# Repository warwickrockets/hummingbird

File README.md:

# Hummingbird

There will eventually be three folders here: ./sims for simulations (Matlab/Simulink mostly), ./myRIO for control software written for the NI MyRIO (might be Labview VIs, C/C++, or a hideous mixture of the two if that's possible), and ./teensy for control software written for a Teensy-3.1-based flight computer. For now, there's just a README. Ho hum.

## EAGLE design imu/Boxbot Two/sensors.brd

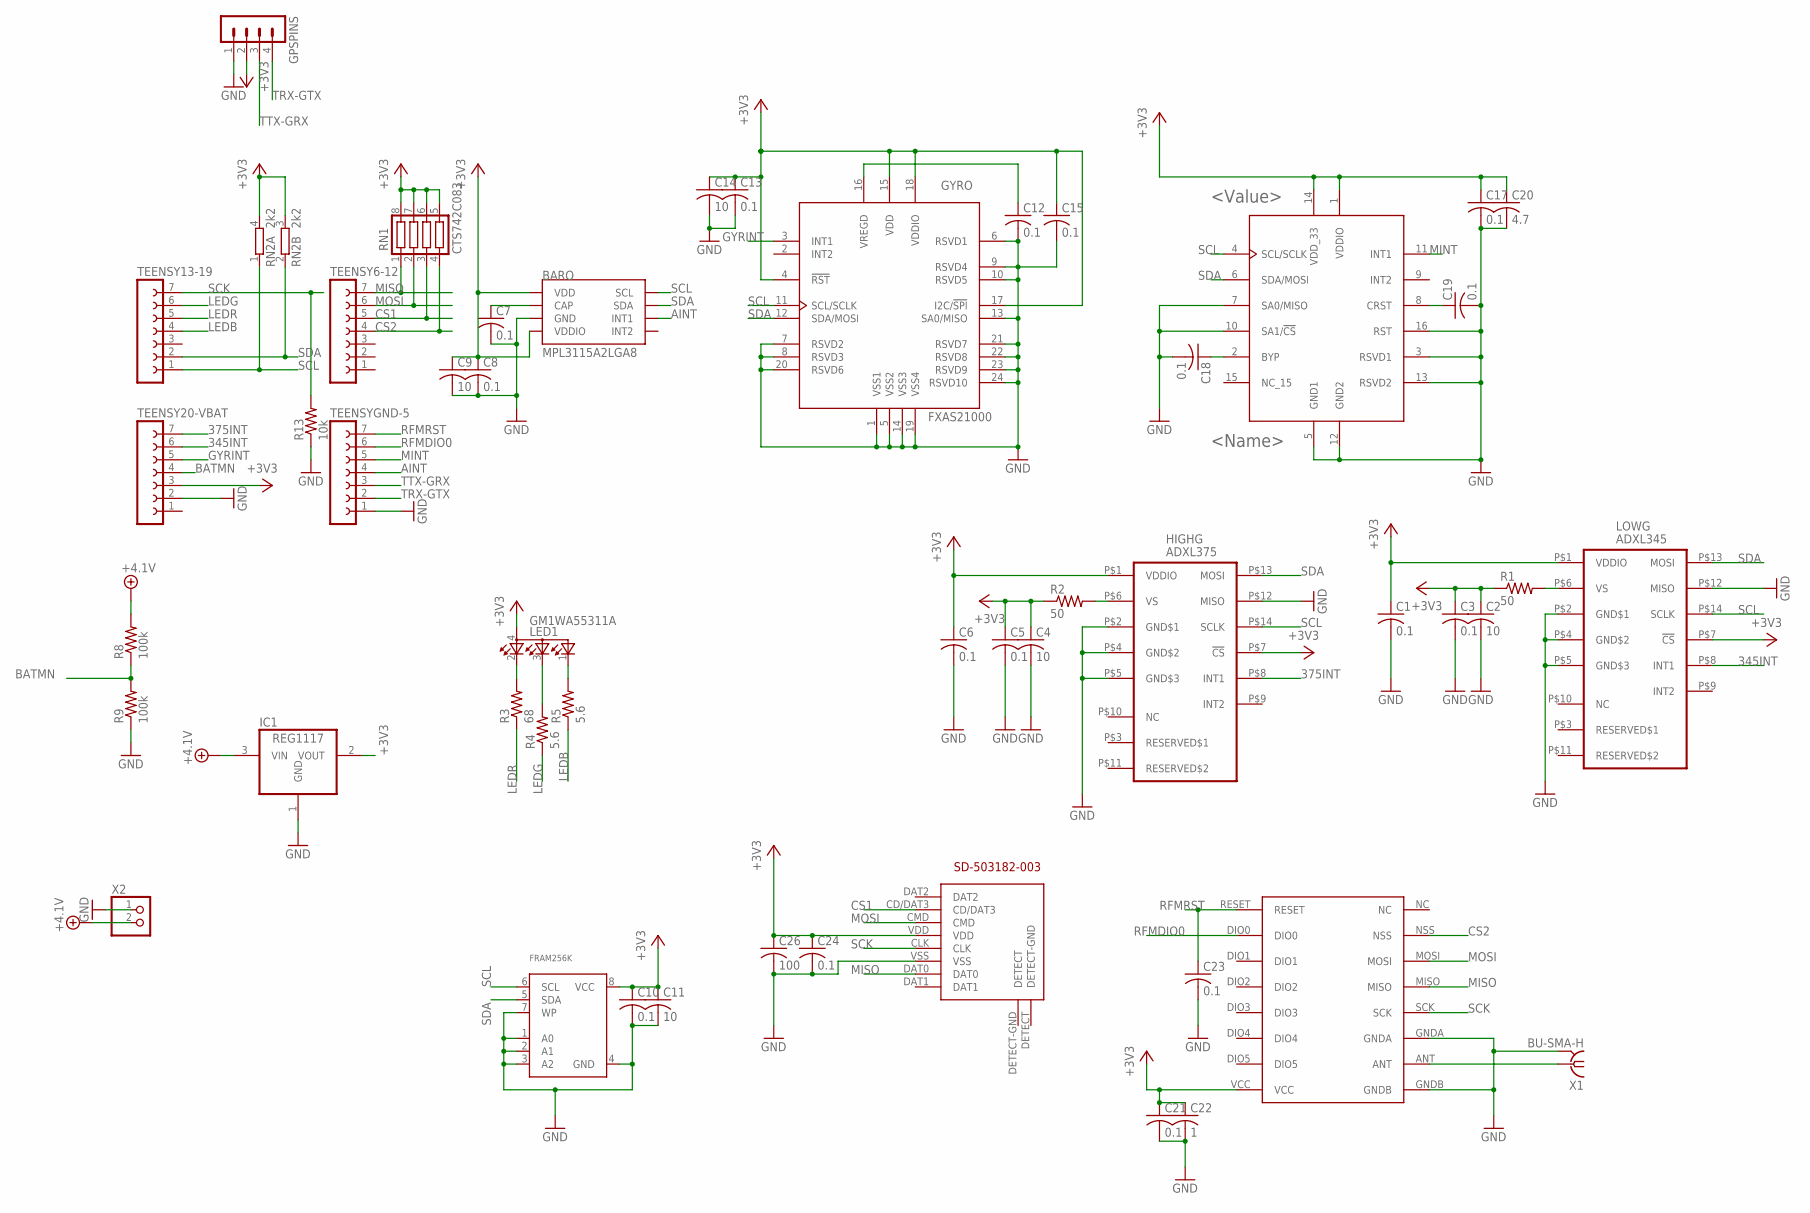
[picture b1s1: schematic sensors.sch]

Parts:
BARO: MPL3115A2LGA8; LGA8
C1, C3, C5, C6, C7, C8, C10, C12, C13, C15, C17, C18, C19, C21, C23, C24: 0.1; C0603
C2, C4, C9, C11, C14: 10; C0805
C20: 4.7; C0805
C22: 1; C0805
C26: 100; C0805
FRAM256K: FRAM_SOIC8_I2C; SOIC8_208MIL
GPSPINS: MA04-1
GYRO: FXAS21000; QFN24_0P5_4X4_ASYM_EXP
HIGHG: ADXL375; LGA14
IC1: REG1117; SOT223
LED1: GM1WA55311A
LOWG: ADXL345; LGA14
MAG: FXOS870CQ; QFN16_0P5_3X3
R1, R2: 50; R0805
R3: 68; R0805
R4, R5: 5.6; R0805
R8, R9: 100k; R0805
R13: 10k; R0805
RN1: CTS742C083
RN2: 2k2; EXBV4V
TEENSY6-12, TEENSY13-19, TEENSY20-VBAT: FE07-1; FE07
TEENSYGND-5: FE07-1; FE07
U$1: SD-503182-003
U$2: RFM69HW; RFM
X1: BU-SMA-H
X2: CON_JST_PH_2PIN; JSTPH2

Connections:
345INT: LOWG.P$8 (INT1), TEENSY20-VBAT.6
375INT: HIGHG.P$8 (INT1), TEENSY20-VBAT.7
+3V3: BARO.1 (VDD), BARO.4 (VDDIO), C1.1, C2.1, C3.1, C4.1, C5.1, C6.1, C8.1, C9.1, C10.1, C11.1, C13.1, C14.1, C15.1, C17.1, C20.1, C21.1, C22.1, C24.1, C26.1, FRAM256K.8 (VCC), GPSPINS.2, GYRO.4 (!RST), GYRO.15 (VDD), GYRO.17 (I2C/!SPI), GYRO.18 (VDDIO), HIGHG.P$1 (VDDIO), HIGHG.P$7 (!CS), IC1.2 (VOUT), LED1.4 (A), LOWG.P$1 (VDDIO), LOWG.P$7 (!CS), MAG.1 (VDDIO), MAG.14 (VDD_33), R1.1, R2.1, RN1.5, RN1.6, RN1.7, RN1.8, RN2.3 (2), RN2.4 (2), TEENSY20-VBAT.3, U$1.VDD, U$2.VCC
+4.1V: IC1.3 (VIN), R8.2, X2.2
AINT: BARO.6 (INT1), TEENSYGND-5.4
BATMN: R8.1, R9.2, TEENSY20-VBAT.4
CS1: RN1.3, TEENSY6-12.5, U$1.CD/DAT3
CS2: RN1.4, TEENSY6-12.4, U$2.NSS
GND: BARO.3 (GND), C1.2, C2.2, C3.2, C4.2, C5.2, C6.2, C7.2, C8.2, C9.2, C10.2, C11.2, C12.2, C13.2, C14.2, C15.2, C17.2, C18.2, C19.2, C20.2, C21.2, C22.2, C23.2, C24.2, C26.2, FRAM256K.1 (A0), FRAM256K.2 (A1), FRAM256K.3 (A2), FRAM256K.4 (GND), FRAM256K.7 (WP), GPSPINS.1, GYRO.1 (VSS1), GYRO.5 (VSS2), GYRO.6 (RSVD1), GYRO.7 (RSVD2), GYRO.8 (RSVD3), GYRO.9 (RSVD4), GYRO.10 (RSVD5), GYRO.13 (SA0/MISO), GYRO.14 (VSS3), GYRO.19 (VSS4), GYRO.20 (RSVD6), GYRO.21 (RSVD7), GYRO.22 (RSVD8), GYRO.23 (RSVD9), GYRO.24 (RSVD10), HIGHG.P$2 (GND$1), HIGHG.P$4 (GND$2), HIGHG.P$5 (GND$3), HIGHG.P$12 (MISO), IC1.1 (GND), LOWG.P$2 (GND$1), LOWG.P$4 (GND$2), LOWG.P$5 (GND$3), LOWG.P$12 (MISO), MAG.3 (RSVD1), MAG.5 (GND1), MAG.7 (SA0/MISO), MAG.10 (SA1/!CS), MAG.12 (GND2), MAG.13 (RSVD2), MAG.16 (RST), R9.1, R13.1, TEENSY20-VBAT.2, TEENSYGND-5.1, U$1.VSS, U$2.GNDA, U$2.GNDB, X1.2, X1.3 (2), X1.4 (2), X1.5 (2), X2.1
GYRINT: GYRO.3 (INT1), TEENSY20-VBAT.5
LEDB: R5.1, TEENSY13-19.4
LEDG: R4.1, TEENSY13-19.6
LEDR: R3.1, TEENSY13-19.5
MINT: MAG.11 (INT1), TEENSYGND-5.5
MISO: RN1.1, TEENSY6-12.7, U$1.DAT0, U$2.MISO
MOSI: RN1.2, TEENSY6-12.6, U$1.CMD, U$2.MOSI
unnamed: LOWG.P$6 (VS), R1.2
unnamed: HIGHG.P$6 (VS), R2.2
unnamed: LED1.2 (CRED), R3.2
unnamed: C18.1, MAG.2 (BYP)
unnamed: LED1.3 (CBLUE), R4.2
unnamed: LED1.1 (CGREEN), R5.2
unnamed: BARO.2 (CAP), C7.1
unnamed: C12.1, GYRO.16 (VREGD)
unnamed: C19.1, MAG.8 (CRST)
unnamed: U$2.ANT, X1.1
RFMDIO0: TEENSYGND-5.6, U$2.DIO0
RFMRST: C23.1, TEENSYGND-5.7, U$2.RESET
SCK: R13.2, TEENSY13-19.7, U$1.CLK, U$2.SCK
SCL: BARO.8 (SCL), FRAM256K.6 (SCL), GYRO.11 (SCL/SCLK), HIGHG.P$14 (SCLK), LOWG.P$14 (SCLK), MAG.4 (SCL/SCLK), RN2.1, TEENSY13-19.1
SDA: BARO.7 (SDA), FRAM256K.5 (SDA), GYRO.12 (SDA/MOSI), HIGHG.P$13 (MOSI), LOWG.P$13 (MOSI), MAG.6 (SDA/MOSI), RN2.2 (1), TEENSY13-19.2
TRX-GTX: GPSPINS.4, TEENSYGND-5.2
TTX-GRX: GPSPINS.3, TEENSYGND-5.3

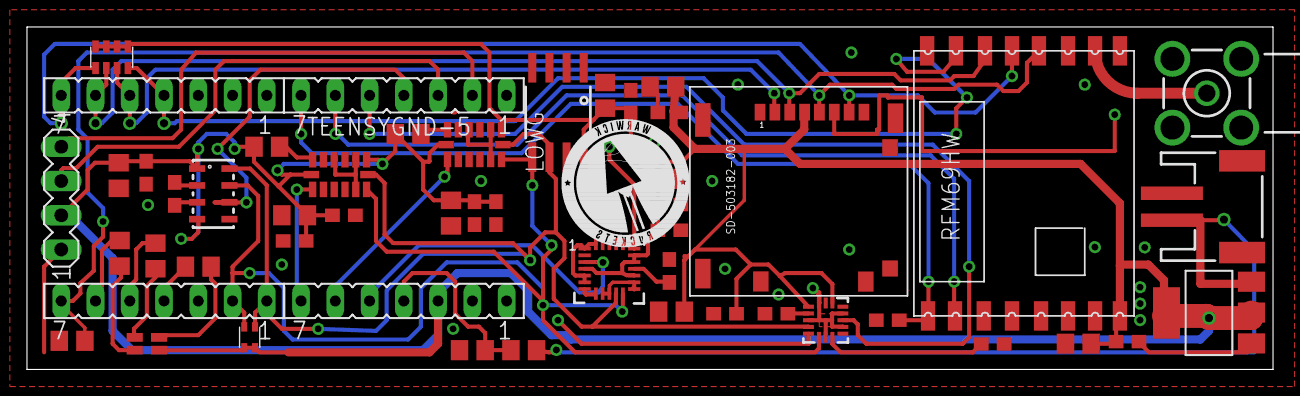
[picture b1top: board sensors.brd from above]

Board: 2 copper layers, 92.4 x 25.4 mm, 51 parts (0 on the bottom side), 33 nets.

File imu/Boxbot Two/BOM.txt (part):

Partlist exported from F:/Warwick Spaceflight/Projects/Hummingbird/Github/hummingbird/imu/Boxbot Two/sensors.sch at 14/06/2015 19:09:03

Part          Value         Device          Package                Description                                                     MF MPN     OC_FARNELL OC_NEWARK
BARO          MPL3115A2LGA8 MPL3115A2LGA8   LGA8                   Altimeter/Pressure Sensor, I2C, 1.95V-3.6V supply, 50 to 110kPa                                
C1            0.1           C-USC0603       C0603                  CAPACITOR, American symbol                                                                     
C2            10            C-USC0805       C0805                  CAPACITOR, American symbol                                                                     
C3            0.1           C-USC0603       C0603                  CAPACITOR, American symbol                                                                     
C4            10            C-USC0805       C0805                  CAPACITOR, American symbol                                                                     
C5            0.1           C-USC0603       C0603                  CAPACITOR, American symbol                                                                     
C6            0.1           C-USC0603       C0603                  CAPACITOR, American symbol                                                                     
C7            0.1           C-USC0603       C0603                  CAPACITOR, American symbol                                                                     
C8            0.1           C-USC0603       C0603                  CAPACITOR, American symbol                                                                     
C9            10            C-USC0805       C0805                  CAPACITOR, American symbol                                                                     
C10           0.1           C-USC0603       C0603                  CAPACITOR, American symbol                                                                     
C11           10            C-USC0805       C0805                  CAPACITOR, American symbol                                                                     
C12           0.1           C-USC0603       C0603                  CAPACITOR, American symbol                                                                     
C13           0.1           C-USC0603       C0603                  CAPACITOR, American symbol                                                                     
C14           10            C-USC0805       C0805                  CAPACITOR, American symbol                                                                     
C15           0.1           C-USC0603       C0603                  CAPACITOR, American symbol                                                                     
C17           0.1           C-USC0603       C0603                  CAPACITOR, American symbol                                                                     
C18           0.1           C-USC0603       C0603                  CAPACITOR, American symbol                                                                     
C19           0.1           C-USC0603       C0603                  CAPACITOR, American symbol                                                                     
C20           4.7           C-USC0805       C0805                  CAPACITOR, American symbol                                                                     
C21           0.1           C-USC0603       C0603                  CAPACITOR, American symbol                                                                     
C22           1             C-USC0805       C0805                  CAPACITOR, American symbol                                                                     
C23           0.1           C-USC0603       C0603                  CAPACITOR, American symbol                                                                     
C24           0.1           C-USC0603       C0603                  CAPACITOR, American symbol                                                                     
C26           100           C-USC0805       C0805                  CAPACITOR, American symbol                                                                     
FRAM256K                    FRAM_SOIC8_I2C  SOIC8_208MIL           I2C FRAM - SOIC8 Package                                                                       
GPSPINS                     MA04-1          MA04-1                 PIN HEADER                                                                 unknown    unknown  
GYRO          FXAS21000     FXAS21000       QFN24_0P5_4X4_ASYM_EXP Xtrinsic FXAS21000 3-Axis Rate Digital Gyroscope                                               
HIGHG         ADXL375       ADXL345         LGA14                  3-Axis, ±2 g/±4 g/±8 g/±16 g Digital Accelerometer                                             
IC1           REG1117       REG1117         SOT223                 800mA and 1A Low Dropout (LDO) Positive Regulator                  REG1117 1097566    14P6981  
LED1          GM1WA55311A   GM1WA55311A     GM1WA55311A            Chip LED RGB                                                                                   
LOWG          ADXL345       ADXL345         LGA14                  3-Axis, ±2 g/±4 g/±8 g/±16 g Digital Accelerometer                                             
MAG           FXOS870CQ     FXOS870CQ       QFN16_0P5_3X3                                                                                                         
R1            50            R-US_R0805      R0805                  RESISTOR, American symbol                                                                      
R2            50            R-US_R0805      R0805                  RESISTOR, American symbol                                                                      
R3            68            R-US_R0805      R0805                  RESISTOR, American symbol                                                                      
R4            5.6           R-US_R0805      R0805                  RESISTOR, American symbol                                                                      
R5            5.6           R-US_R0805      R0805                  RESISTOR, American symbol                                                                      
R8            100k          R-US_R0805      R0805                  RESISTOR, American symbol                                                                      
R9            100k          R-US_R0805      R0805                  RESISTOR, American symbol                                                                      
R13           10k           R-US_R0805      R0805                  RESISTOR, American symbol                                                                      
RN1           CTS742C083    CTS742C083      CTS742C083             Chip Resistor Array 4 Single Resistor                                      unknown    unknown  
RN2           2k2           2R-NEXBV4V      EXBV4V                 Array Chip Resistor                                                        unknown    unknown  
TEENSY6-12                  FE07-1          FE07                   FEMALE HEADER                                                              unknown    unknown  
TEENSY13-19                 FE07-1          FE07                   FEMALE HEADER                                                              unknown    unknown  
TEENSY20-VBAT               FE07-1          FE07                   FEMALE HEADER                                                              unknown    unknown  
TEENSYGND-5                 FE07-1          FE07                   FEMALE HEADER                                                              unknown    unknown  
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
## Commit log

2015-01-24 Added an old simulation from ages ago.
    1D flight for various structural masses. Yay for unthrottleable motors!
2015-04-10 Started plonking stuff down
    Little progress yet, because still hunting for available parts. Nothing
    has yet been connected.
2015-09-30 Oops, I forgot how Git works
    Yeah, that. More accurately, I forgot to use it! Fixed now.
